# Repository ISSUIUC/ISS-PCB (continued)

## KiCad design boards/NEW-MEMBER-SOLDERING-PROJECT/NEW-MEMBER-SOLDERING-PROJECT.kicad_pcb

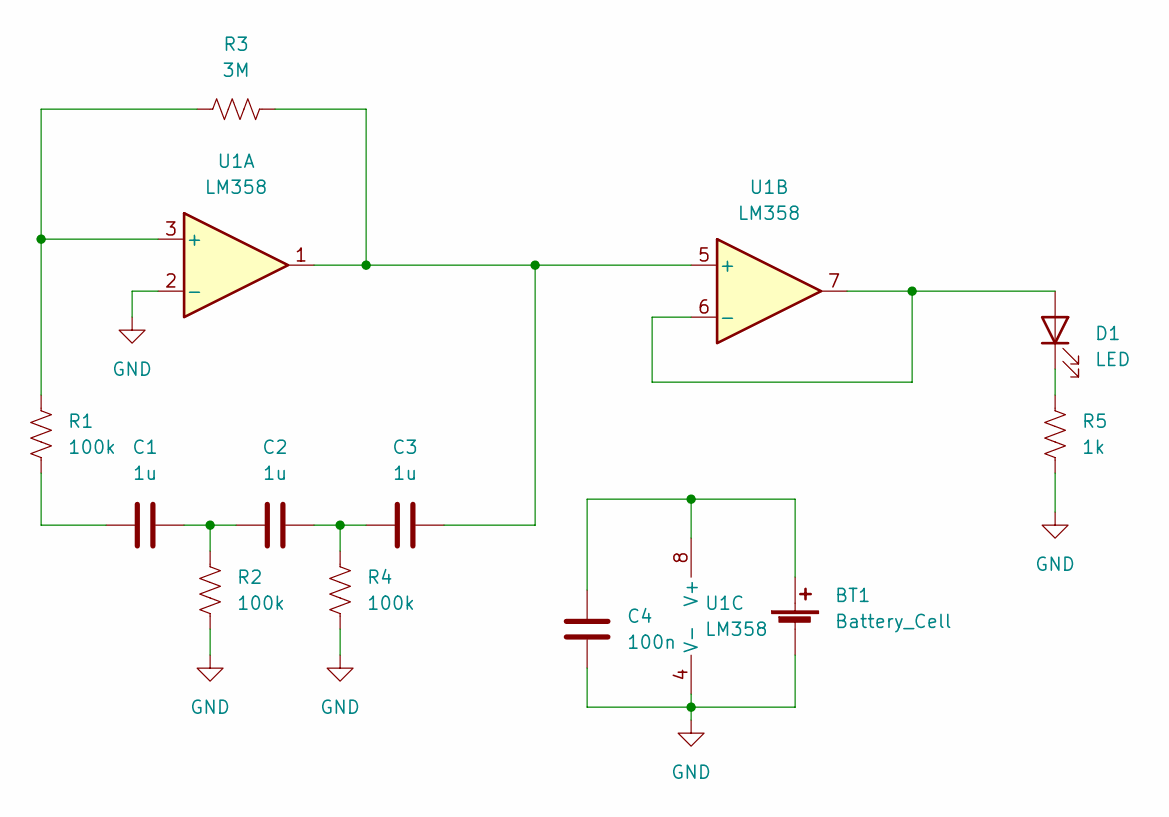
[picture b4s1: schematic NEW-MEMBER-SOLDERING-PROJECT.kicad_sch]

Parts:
BT1: Battery_Cell; Battery_Adam_Tech_BH-67D-5
C1, C2, C3: 1u; C_0805_2012Metric
C4: 100n; C_0805_2012Metric
D1: LED; LED_0805_2012Metric
R1, R2, R4: 100k; R_0805_2012Metric
R3: 3M; R_0805_2012Metric
R5: 1k; R_0805_2012Metric
U1: LM358; SOIC-8_3.9x4.9mm_P1.27mm

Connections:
GND: BT1.2 (-), C4.1, R2.1, R4.1, R5.1, U1.2 (-), U1.4 (V-)
unnamed: BT1.1 (+), C4.2, U1.8 (V+)
unnamed: C1.1, R1.1
unnamed: C1.2, C2.1, R2.2
unnamed: C2.2, C3.1, R4.2
unnamed: C3.2, R3.1, U1.1, U1.5 (+)
unnamed: D1.1 (K), R5.2
unnamed: D1.2 (A), U1.6 (-), U1.7
unnamed: R1.2, R3.2, U1.3 (+)

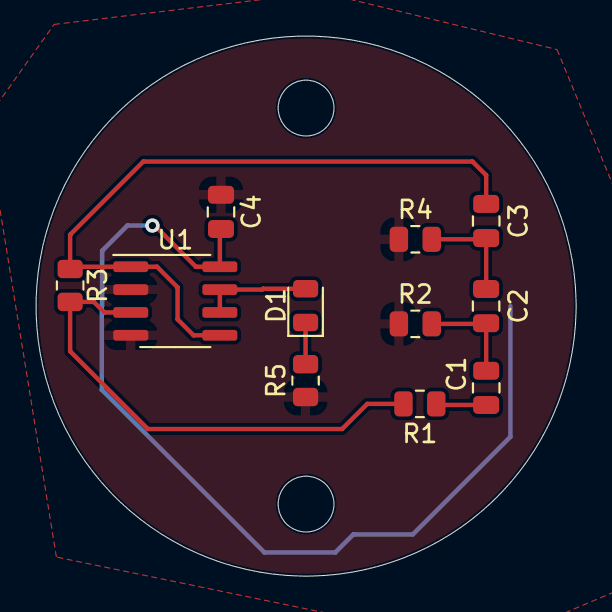
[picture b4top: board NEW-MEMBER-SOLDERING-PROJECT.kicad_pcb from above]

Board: 2 copper layers, 30.0 x 30.0 mm, 12 parts (1 on the bottom side), 9 nets.

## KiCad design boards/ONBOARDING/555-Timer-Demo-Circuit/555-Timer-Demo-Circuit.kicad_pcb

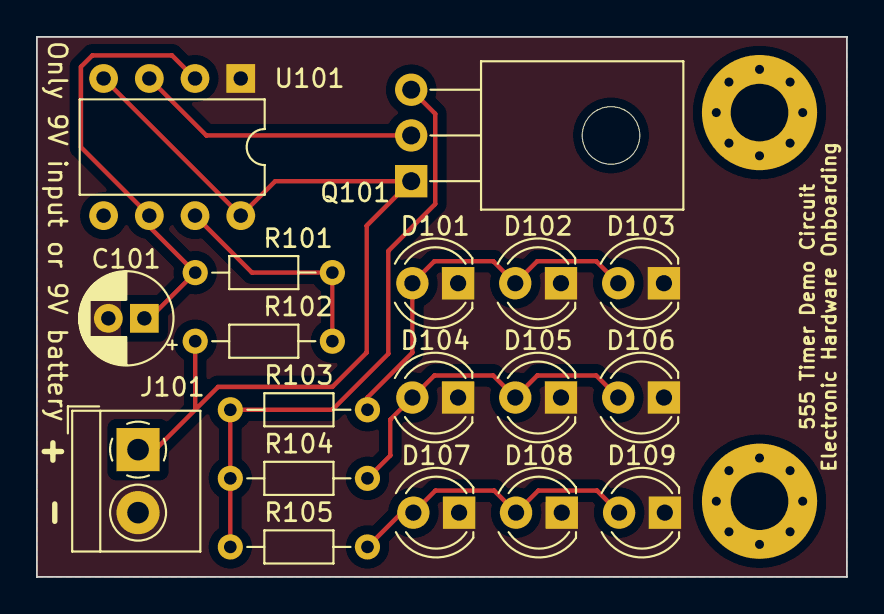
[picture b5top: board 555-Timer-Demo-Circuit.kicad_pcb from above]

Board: 2 copper layers, 45.0 x 30.0 mm, 20 parts (0 on the bottom side), 9 nets.

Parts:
C101: 10uf; CP_Radial_D5.0mm_P2.00mm
D101, D104, D107: Red; LED_D4.0mm
D102, D105, D108: Blue; LED_D4.0mm
D103, D106, D109: Green; LED_D4.0mm
H101, H102: MountingHole; MountingHole_3.2mm_M3_Pad_Via
J101: Terminal Block; TerminalBlock_4Ucon_1x02_P3.50mm_Horizontal
Q101: NMOS; TO-126-3_Horizontal_TabUp
R101, R102: 50K; R_Axial_DIN0204_L3.6mm_D1.6mm_P7.62mm_Horizontal
R103, R104, R105: 500; R_Axial_DIN0204_L3.6mm_D1.6mm_P7.62mm_Horizontal
U101: LM555xN; DIP-8_W7.62mm

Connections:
+9V: J101.1, Q101.1 (D), R102.1, U101.4 (R), U101.8 (VCC)
/THR: C101.1, R101.2, U101.2 (TR), U101.6 (THR)
GND: C101.2, D101.1 (K), D102.1 (K), D103.1 (K), D104.1 (K), D105.1 (K), D106.1 (K), D107.1 (K), D108.1 (K), D109.1 (K), J101.2, U101.1 (GND)
unnamed: D101.2 (A), D102.2 (A), D103.2 (A), R103.2
unnamed: D104.2 (A), D105.2 (A), D106.2 (A), R104.2
unnamed: D107.2 (A), D108.2 (A), D109.2 (A), R105.2
unnamed: Q101.2 (G), U101.3 (Q)
unnamed: Q101.3 (S), R103.1, R104.1, R105.1
unnamed: R101.1, R102.2, U101.7 (DIS)

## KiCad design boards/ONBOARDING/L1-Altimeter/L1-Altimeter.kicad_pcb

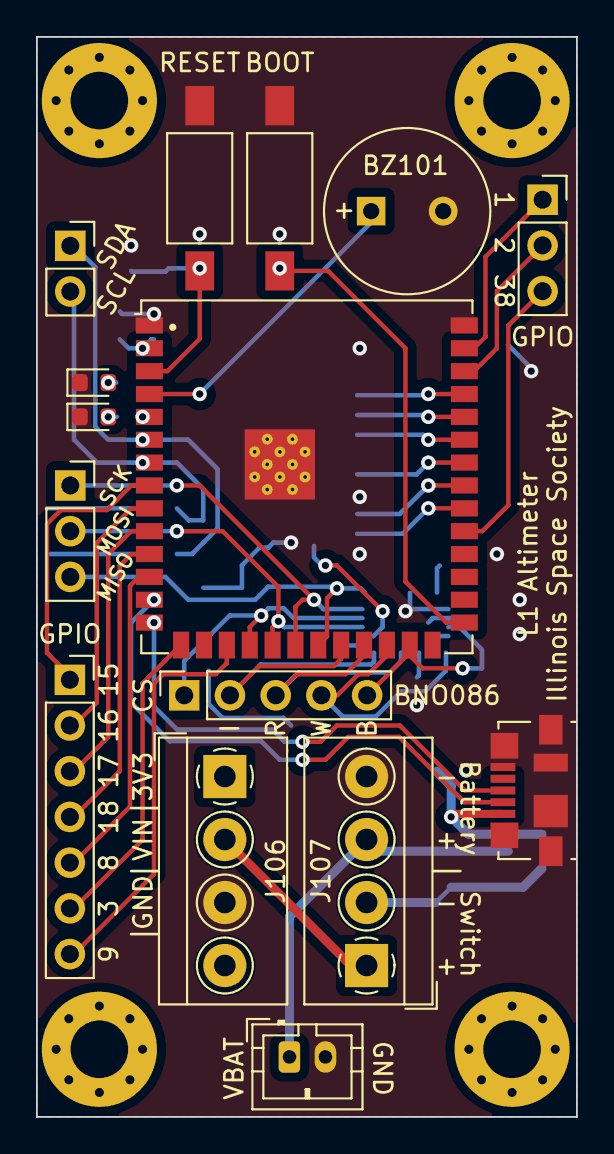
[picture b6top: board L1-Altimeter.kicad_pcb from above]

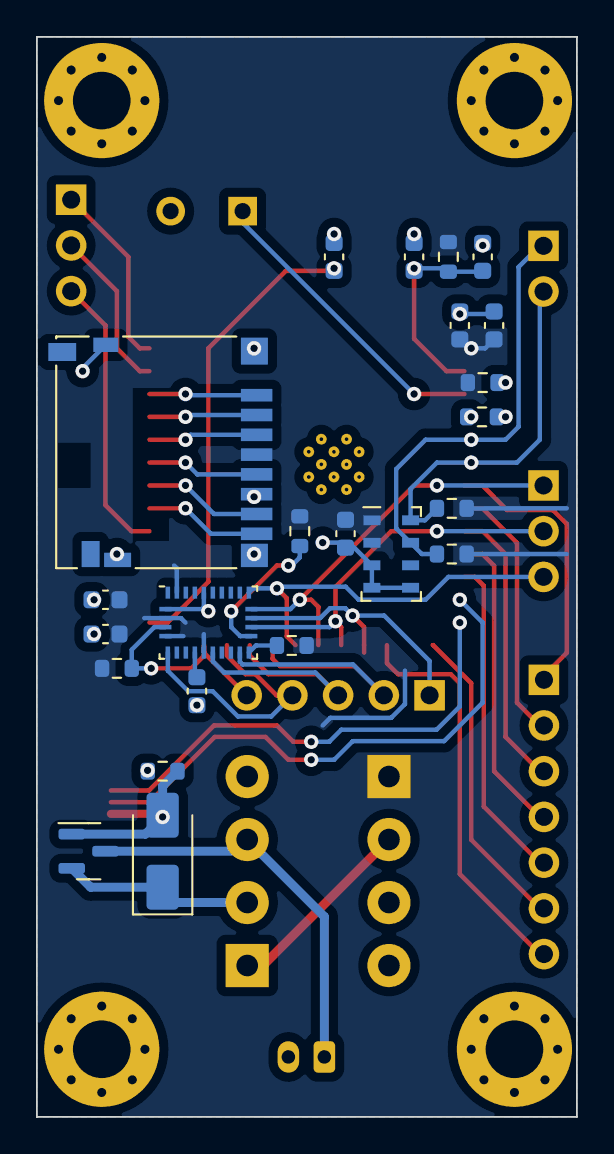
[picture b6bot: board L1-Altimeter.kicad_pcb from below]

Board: 2 copper layers, 30.0 x 60.0 mm, 42 parts (23 on the bottom side), 43 nets.

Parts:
BZ101: AT-0927-TT-6-R; MagneticBuzzer_PUI_AT-0927-TT-6-R
C101, C103, C104, C105, C106, C108, C109: 0.1uF; C_0603_1608Metric
C102: 22uF; C_0603_1608Metric
C107: 1uF; C_0603_1608Metric
D101: RED LED; LED_0603_1608Metric
D102: BLUE LED; LED_0603_1608Metric
D103: MBRA340; D_SMA
H101, H102, H103, H104: M3; MountingHole_3.2mm_M3_Pad_Via
J101: DM3D-SF; microSD_HC_Hirose_DM3D-SF
J102: Terminal Block; JST_PH_B2B-PH-K_1x02_P2.00mm_Vertical
J103: USB4105-GF-A; USB_Micro-B_Molex_47346-0001
J104: Conn_01x07; PinSocket_1x07_P2.54mm_Vertical
J105, J110: PinSocket_1x03_P2.54mm_Vertical
J106: Left; TerminalBlock_4Ucon_1x04_P3.50mm_Horizontal
J107: Right; TerminalBlock_4Ucon_1x04_P3.50mm_Horizontal
J108: Conn_01x05; PinSocket_1x05_P2.54mm_Vertical
J109: Conn_01x02; PinSocket_1x02_P2.54mm_Vertical
Q101: DMG2301L; SOT-23
R101, R102, R103, R107: 10k; R_0603_1608Metric
R104, R105: 470; R_0603_1608Metric
R106, R108: 2.2k; R_0603_1608Metric
R109: 100k; R_0603_1608Metric
SW101, SW102: SW_Push; SW_SPST_FSMSM
U101: ESP32-S3-WROOM-1U
U102: MS5611-01BA03; LGA-8_3x5mm_P1.25mm
U103: BNO086; LGA-28_5.2x3.8mm_P0.5mm

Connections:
+3V3: C102.1, C104.1, C105.1, C108.1, C109.1, J101.4 (VDD), J106.1, R101.2, R102.2, R103.2, R104.1, R106.2, R107.2, R108.2, U101.2 (3V3), U102.1 (VDD), U102.2 (PS), U103.3 (VDD), U103.5 (PS1), U103.10 (CLKSEL0), U103.28 (VDDIO)
/BNO086_BOOT: J108.5, R103.1, U101.25 (IO48), U103.4 (BOOTN)
/BNO086_CS: J108.1, U101.18 (IO10), U103.18 (H_CSN)
/BNO086_INT: J108.2, U101.22 (IO14), U103.14 (H_INTN)
/BNO086_RESET: J108.3, U101.23 (IO21), U103.11 (NRST)
/BNO086_WAKE: J108.4, U101.24 (IO47), U103.6 (PS0/WAKE)
/BOOT_SW: C101.2, SW101.2, U101.27 (IO0)
/BUZZER: BZ101.1 (-), U101.4 (IO4)
/GPIO1: J105.1, U101.39 (IO1)
/GPIO2: J105.2, U101.38 (IO2)
/GPIO3: J104.6, U101.15 (IO3)
/GPIO8: J104.5, U101.12 (IO8)
/GPIO9: J104.7, U101.17 (IO9)
/GPIO15: J104.1, U101.8 (IO15)
/GPIO16: J104.2, U101.9 (IO16)
/GPIO17: J104.3, U101.10 (IO17)
/GPIO18: J104.4, U101.11 (IO18)
/GPIO38: J105.3, U101.31 (IO38)
/I2C_SCL: J109.2, R102.1, U101.7 (IO7), U102.8 (SCLK)
/I2C_SDA: J109.1, R101.1, U101.6 (IO6), U102.7 (SDI/SDA)
/LED_BLUE: R105.1, U101.5 (IO5)
/MicroSD_CLK: J101.5 (CLK), U101.34 (IO41)
/MicroSD_CMD: J101.3 (CMD), U101.35 (IO42)
/MicroSD_DAT0: J101.7 (DAT0), U101.33 (IO40)
/MicroSD_DAT1: J101.8 (DAT1), U101.32 (IO39)
/MicroSD_DAT2: J101.1 (DAT2), U101.37 (TXD0)
/MicroSD_DAT3: J101.2 (DAT3/CD), U101.36 (RXD0)
/RESET_SW: C103.1, C107.1, R107.1, SW102.1, U101.3 (EN)
/SPI_MISO: J110.3, U101.21 (IO13), U103.20 (H_SDA/H_MISO/TX)
/SPI_MOSI: J110.2, U101.19 (IO11), U103.17 (H_SA0_MOSI)
/SPI_SCK: J110.1, U101.20 (IO12), U103.19 (H_SCL/SCK/RX)
/USB_D+: J103.3 (D+), U101.14 (IO20)
/USB_D-: J103.2 (D-), U101.13 (IO19)
/VBAT: J102.1, J107.3, Q101.3 (D)
/VBUS: D103.2 (A), J103.1 (VBUS), Q101.1 (G), R109.1
/VIN: J106.2, J107.1
/VSYS: D103.1 (K), J107.2, Q101.2 (S)
GND: BZ101.2 (+), C101.1, C102.2, C103.2, C104.2, C105.2, C106.2, C107.2, C108.2, C109.2, D101.1 (K), D102.1 (K), J101.6 (VSS), J101.11 (SHIELD), J102.2, J103.5 (GND), J103.6 (Shield), J106.3, J107.4, R109.2, SW101.1, SW102.2, U101.1 (GND), U101.40 (GND), U101.41 (EPAD), U102.3 (GND), U102.4 (CSB), U102.5 (CSB), U103.2 (GND), U103.25 (GNDIO)
unnamed: D101.2 (A), R104.2
unnamed: D102.2 (A), R105.2
unnamed: C106.1, U103.9 (CAP)
unnamed: R108.1, U103.15 (ENV_SCL)
unnamed: R106.1, U103.16 (ENV_SDA)
